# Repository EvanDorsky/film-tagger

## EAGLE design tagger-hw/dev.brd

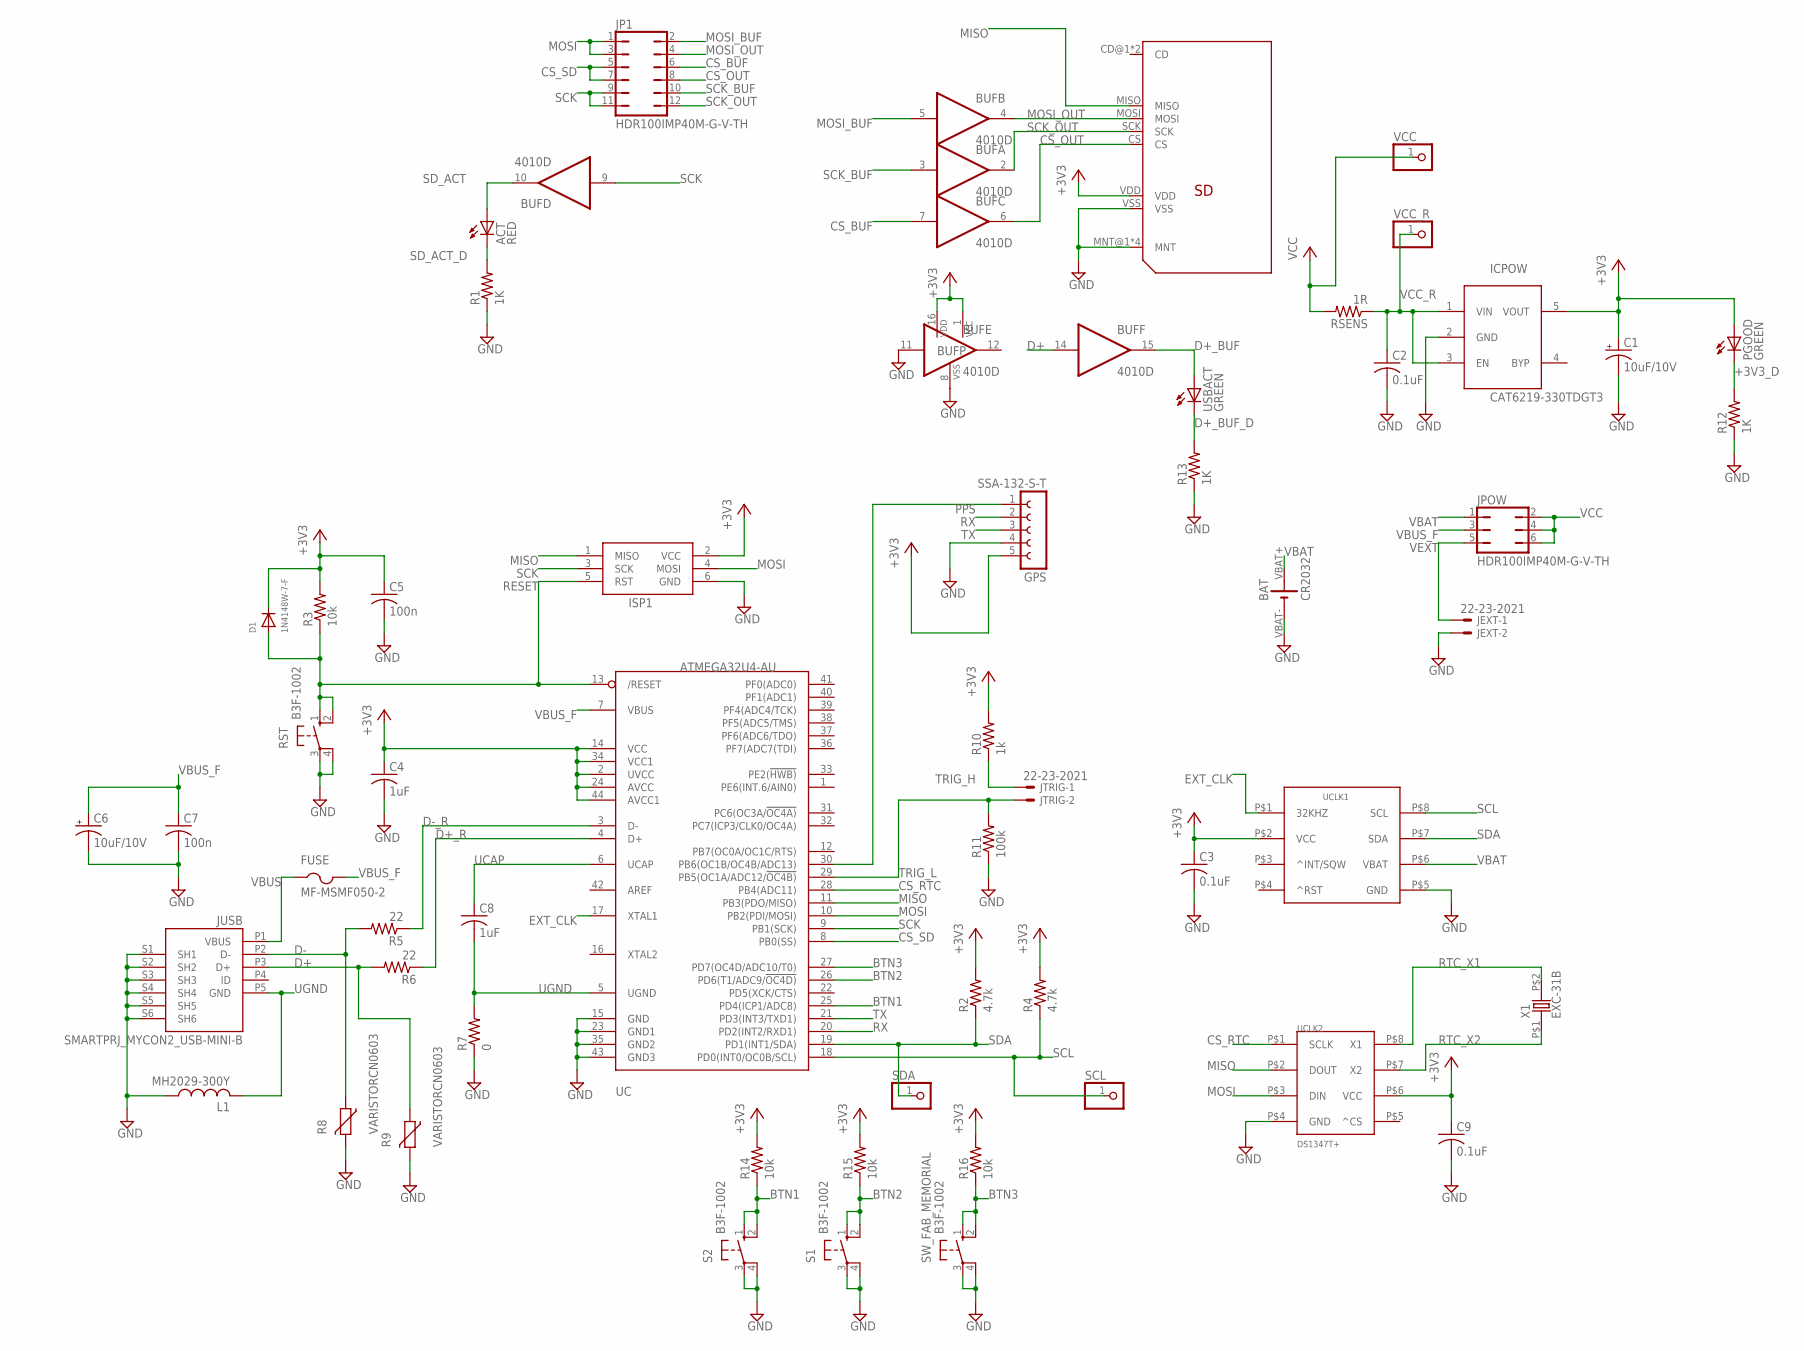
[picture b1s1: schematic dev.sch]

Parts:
ACT: RED; CHIP-LED0603
BAT: CR2032; BS-7
BUF: 4010D; SO16
C1, C6: 10uF/10V; A/3216-18R
C2, C3, C9: 0.1uF; C0603K
C4, C8: 1uF; C0603
C5, C7: 100n; C0603
D1: 1N4148W-7-F; SOD-123
FUSE: MF-MSMF050-2; 1812
GPS: SSA-132-S-T; FE05-1
ICPOW: CAT6219-330TDGT3; SOT23-5L
ISP1: AVRISP-6; AVRISP
JEXT: 22-23-2021
JP1: HDR100IMP40M-G-V-TH; JP6Q
JPOW: HDR100IMP40M-G-V-TH; JP3Q
JTRIG: 22-23-2021
JUSB: SMARTPRJ_MYCON2_USB-MINI-B; SMARTPRJ_CON2_USB_MICRO_B_AT
L1: MH2029-300Y; C0805
PGOOD: GREEN; CHIP-LED0603
R1, R12, R13: 1K; R0603
R2, R4: 4.7k; R0603
R3, R14, R15, R16: 10k; R0603
R5, R6: 22; R0603
R7: 0; R0603
R8, R9: VARISTORCN0603; CT/CN0603
R10: 1k; R0603
R11: 100k; R0603
RSENS: 1R; R0603
RST: B3F-1002; B3F-10XX
S1, S2: B3F-1002; B3F-10XX
SCL: PINHD-1X1; 1X01
SDA: PINHD-1X1; 1X01
SW_FAB_MEMORIAL: B3F-1002; B3F-10XX
U$1: MICROSD
UC: ATMEGA32U4-AU; TQFP44
UCLK1: DS3231MDS3231MZ+; S8MK+1
UCLK2: DS1347T+; 8_TDFN-EP
USBACT: GREEN; CHIP-LED0603
VCC: PINHD-1X1; 1X01
VCC_R: PINHD-1X1; 1X01
X1: EXC-31B; XTAL-SM2

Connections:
+3V3: BUF.1 (VCC), BUF.16 (VDD), C1.+, C3.1, C4.1, C5.1, C9.1, D1.C, GPS.5, ICPOW.5 (VOUT), ISP1.2 (VCC), PGOOD.A, R2.2, R3.2, R4.2, R10.2, R14.2, R15.2, R16.2, U$1.VDD, UC.2 (UVCC), UC.14 (VCC), UC.24 (AVCC), UC.34 (VCC1), UC.44 (AVCC1), UCLK1.P$2 (VCC), UCLK2.P$6 (VCC)
+3V3_D: PGOOD.C, R12.2
BTN1: R14.1, S2.1 (S), S2.2 (S1), UC.25 (PD4(ICP1/ADC8))
BTN2: R15.1, S1.1 (S), S1.2 (S1), UC.26 (PD6(T1/ADC9/!OC4D))
BTN3: R16.1, SW_FAB_MEMORIAL.1 (S), SW_FAB_MEMORIAL.2 (S1), UC.27 (PD7(OC4D/ADC10/T0))
CS_BUF: BUF.7 (I), JP1.6
CS_OUT: BUF.6 (O), JP1.8, U$1.CS
CS_RTC: UC.28 (PB4(ADC11)), UCLK2.P$1 (SCLK)
CS_SD: JP1.5, JP1.7, UC.8 (PB0(SS))
D+: BUF.14 (I), JUSB.P3 (D+), R6.2, R9.1
D+_BUF: BUF.15 (O), USBACT.A
D+_BUF_D: R13.2, USBACT.C
D+_R: R6.1, UC.4 (D+)
D-: JUSB.P2 (D-), R5.2, R8.1
D-_R: R5.1, UC.3 (D-)
EXT_CLK: UC.17 (XTAL1), UCLK1.P$1 (32KHZ)
GND: BAT.VBAT- (-), BUF.8 (VSS), BUF.11 (I), C1.-, C2.2, C3.2, C4.2, C5.2, C6.-, C7.2, C9.2, GPS.4, ICPOW.2 (GND), ISP1.6 (GND), JEXT.2, JUSB.S1 (SH1), JUSB.S2 (SH2), JUSB.S3 (SH3), JUSB.S4 (SH4), JUSB.S5 (SH5), JUSB.S6 (SH6), L1.1, R1.1, R7.1, R8.2, R9.2, R11.1, R12.1, R13.1, RST.3, RST.4 (P1), S1.3, S1.4 (P1), S2.3, S2.4 (P1), SW_FAB_MEMORIAL.3, SW_FAB_MEMORIAL.4 (P1), U$1.MNT@1 (MNT), U$1.MNT@2 (MNT), U$1.MNT@3 (MNT), U$1.MNT@4 (MNT), U$1.VSS, UC.15 (GND), UC.23 (GND1), UC.35 (GND2), UC.43 (GND3), UCLK1.P$5 (GND), UCLK2.P$4 (GND)
MISO: ISP1.1 (MISO), U$1.MISO, UC.11 (PB3(PDO/MISO)), UCLK2.P$2 (DOUT)
MOSI: ISP1.4 (MOSI), JP1.1, JP1.3, UC.10 (PB2(PDI/MOSI)), UCLK2.P$3 (DIN)
MOSI_BUF: BUF.5 (I), JP1.2
MOSI_OUT: BUF.4 (O), JP1.4, U$1.MOSI
PPS: GPS.1, UC.30 (PB6(OC1B/OC4B/ADC13))
RESET: D1.A, ISP1.5 (RST), R3.1, RST.1 (S), RST.2 (S1), UC.13 (/RESET)
RTC_X1: UCLK2.P$8 (X1), X1.P$2 (2)
RTC_X2: UCLK2.P$7 (X2), X1.P$1 (1)
RX: GPS.2, UC.20 (PD2(INT2/RXD1))
SCK: BUF.9 (I), ISP1.3 (SCK), JP1.9, JP1.11, UC.9 (PB1(SCK))
SCK_BUF: BUF.3 (I), JP1.10
SCK_OUT: BUF.2 (O), JP1.12, U$1.SCK
SCL: R4.1, SCL.1, UC.18 (PD0(INT0/OC0B/SCL)), UCLK1.P$8 (SCL)
SDA: R2.1, SDA.1, UC.19 (PD1(INT1/SDA)), UCLK1.P$7 (SDA)
SD_ACT: ACT.A, BUF.10 (O)
SD_ACT_D: ACT.C, R1.2
TRIG_H: JTRIG.1, R10.1
TRIG_L: JTRIG.2, R11.2, UC.29 (PB5(OC1A/ADC12/!OC4B))
TX: GPS.3, UC.21 (PD3(INT3/TXD1))
UCAP: C8.1, UC.6 (UCAP)
UGND: C8.2, JUSB.P5 (GND), L1.2, R7.2, UC.5 (UGND)
VBAT: BAT.VBAT+ (+), JPOW.1, UCLK1.P$6 (VBAT)
VBUS: FUSE.1, JUSB.P1 (VBUS)
VBUS_F: C6.+, C7.1, FUSE.2, JPOW.3, UC.7 (VBUS)
VCC: JPOW.2, JPOW.4, JPOW.6, RSENS.2, VCC.1
VCC_R: C2.1, ICPOW.1 (VIN), ICPOW.3 (EN), RSENS.1, VCC_R.1
VEXT: JEXT.1, JPOW.5

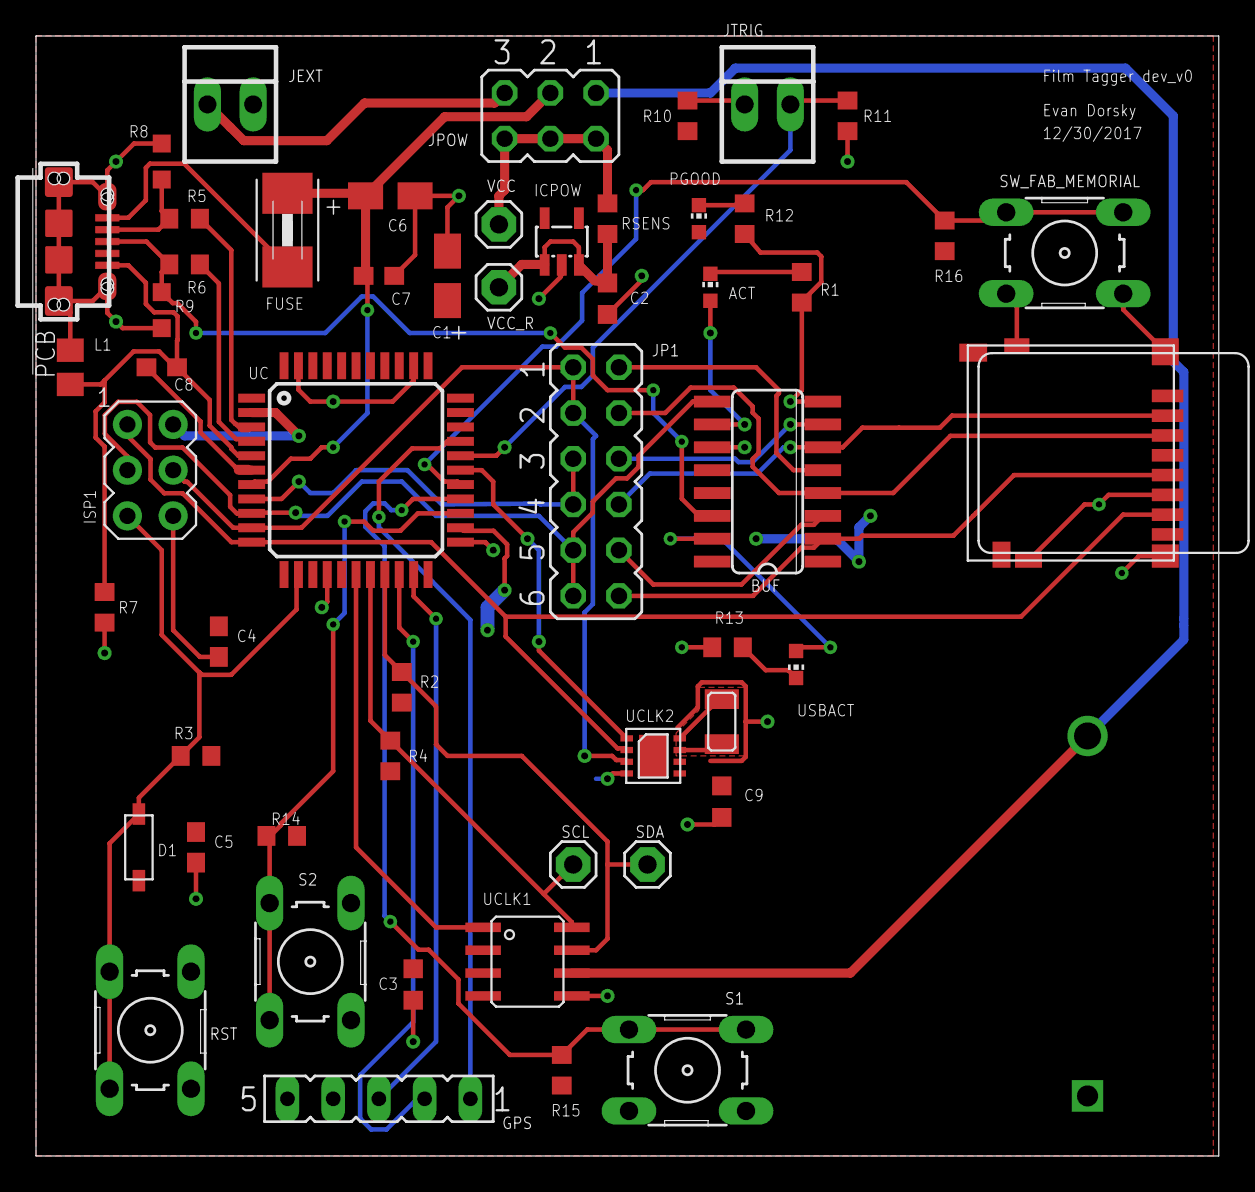
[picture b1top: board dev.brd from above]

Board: 2 copper layers, 65.7 x 62.2 mm, 55 parts (0 on the bottom side), 44 nets.

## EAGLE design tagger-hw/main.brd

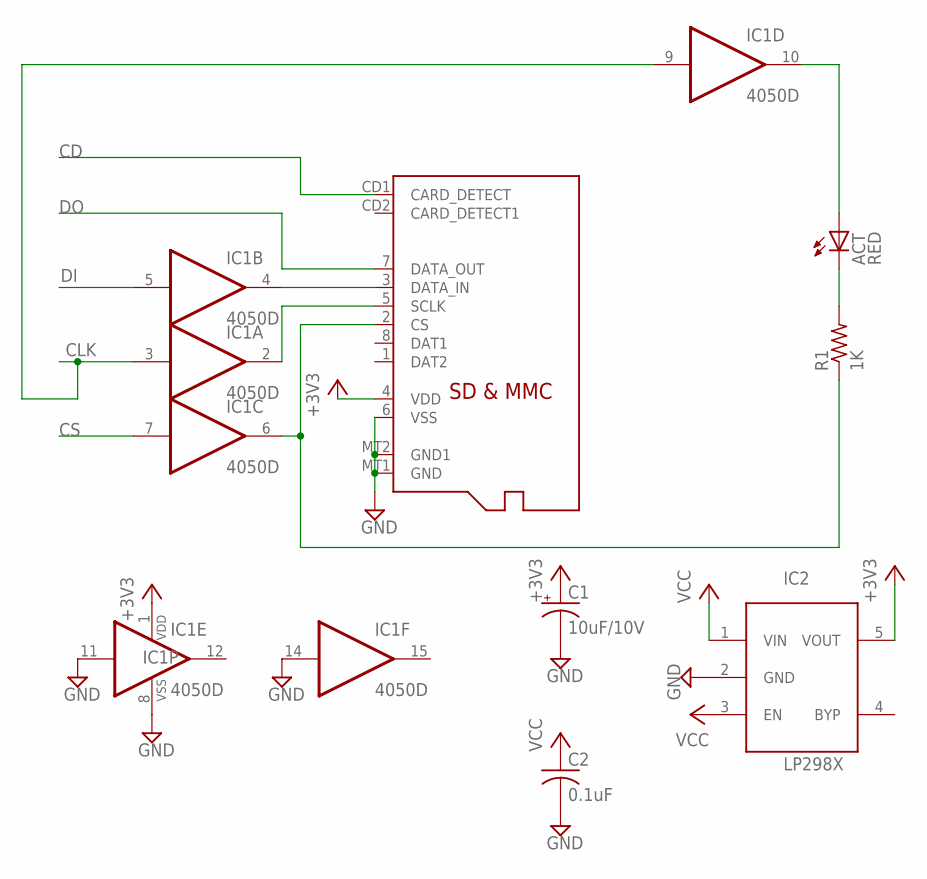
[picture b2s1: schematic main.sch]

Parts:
ACT: RED; CHIP-LED0805
C1: 10uF/10V; A/3216-18R
C2: 0.1uF; C0805K
IC1: 4050D; SO16
IC2: LP298XS; SOT23-5L
R1: 1K; R0805
X1: MICROSD

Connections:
+3V3: C1.+, IC1.1 (VDD), IC2.5 (VOUT), X1.4 (VDD)
CD: X1.CD1 (CARD_DETECT)
CLK: IC1.3 (I), IC1.9 (I)
CS: IC1.7 (I)
DI: IC1.5 (I)
DO: X1.7 (DATA_OUT)
GND: C1.-, C2.2, IC1.8 (VSS), IC1.11 (I), IC1.14 (I), IC2.2 (GND), X1.6 (VSS), X1.MT1 (GND), X1.MT2 (GND1)
unnamed: ACT.A, IC1.10 (O)
unnamed: IC1.2 (O), X1.5 (SCLK)
unnamed: IC1.6 (O), R1.1, X1.2 (CS)
unnamed: ACT.C, R1.2
unnamed: IC1.4 (O), X1.3 (DATA_IN)
VCC: C2.1, IC2.1 (VIN), IC2.3 (EN)

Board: 2 copper layers, 7 parts (0 on the bottom side), 9 nets, no tracks yet.

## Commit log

2017-05-20 SD/GPS test code
2017-05-20 File writing function
2017-05-20 Write to multiple files!
2017-05-20 Use #define for debug
2017-05-21 Simple flash sync trigger works!
2017-06-19 Docs, lots of i2c progress, need to change pins
2017-06-23 Clean up code, set date/time (to around now)!
2017-06-23 We got UTC time!
2017-06-25 Rtc library
2017-06-25 Change SD pin
2017-06-25 Card library, test (not working)
2017-06-25 Module coexistence (and pointer learning)
2017-06-25 Write-on-trigger almost works (not reliable)
2017-06-25 File write on trigger mostly works
2017-06-26 Basic time logging works! Need debouncing
2017-12-17 Add submodules, Eagle project
2017-12-18 Add Arduino example, rename main to dev
2017-12-23 Placement/layout done except for SPI RTC
2017-12-24 Mostly trace width changes
2017-12-28 4010 schematic investigation
2017-12-28 dev_v0 routing/placement lock
2017-12-29 Just kidding, add more buttons and LEDs
2017-12-29 Minor name changes
2017-12-29 More renaming
2017-12-29 Initial dev_v0 BOM export
2017-12-29 Fix some package sizes (0805 -> 0603)
2017-12-30 New microSD slot pattern
2017-12-30 Add current sense resistor, calculations
2017-12-30 Update silk date
2017-12-30 Add some test points
2017-12-30 Switch to CR2032
2017-12-30 dev_v0 BOM ready
2017-12-31 Ensure all drills are above minimum diameter
2017-12-31 Final dev_v0 BOM and cart from order
2017-12-31 Update to a non-esoteric battery holder
2017-12-31 Actual dev_v0 release

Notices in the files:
parts and their libraries:
40xx: Source: www.fairchildsemi.com CD4010.pdf  © 2000 Fairchild Semiconductor Corporation DS005945
